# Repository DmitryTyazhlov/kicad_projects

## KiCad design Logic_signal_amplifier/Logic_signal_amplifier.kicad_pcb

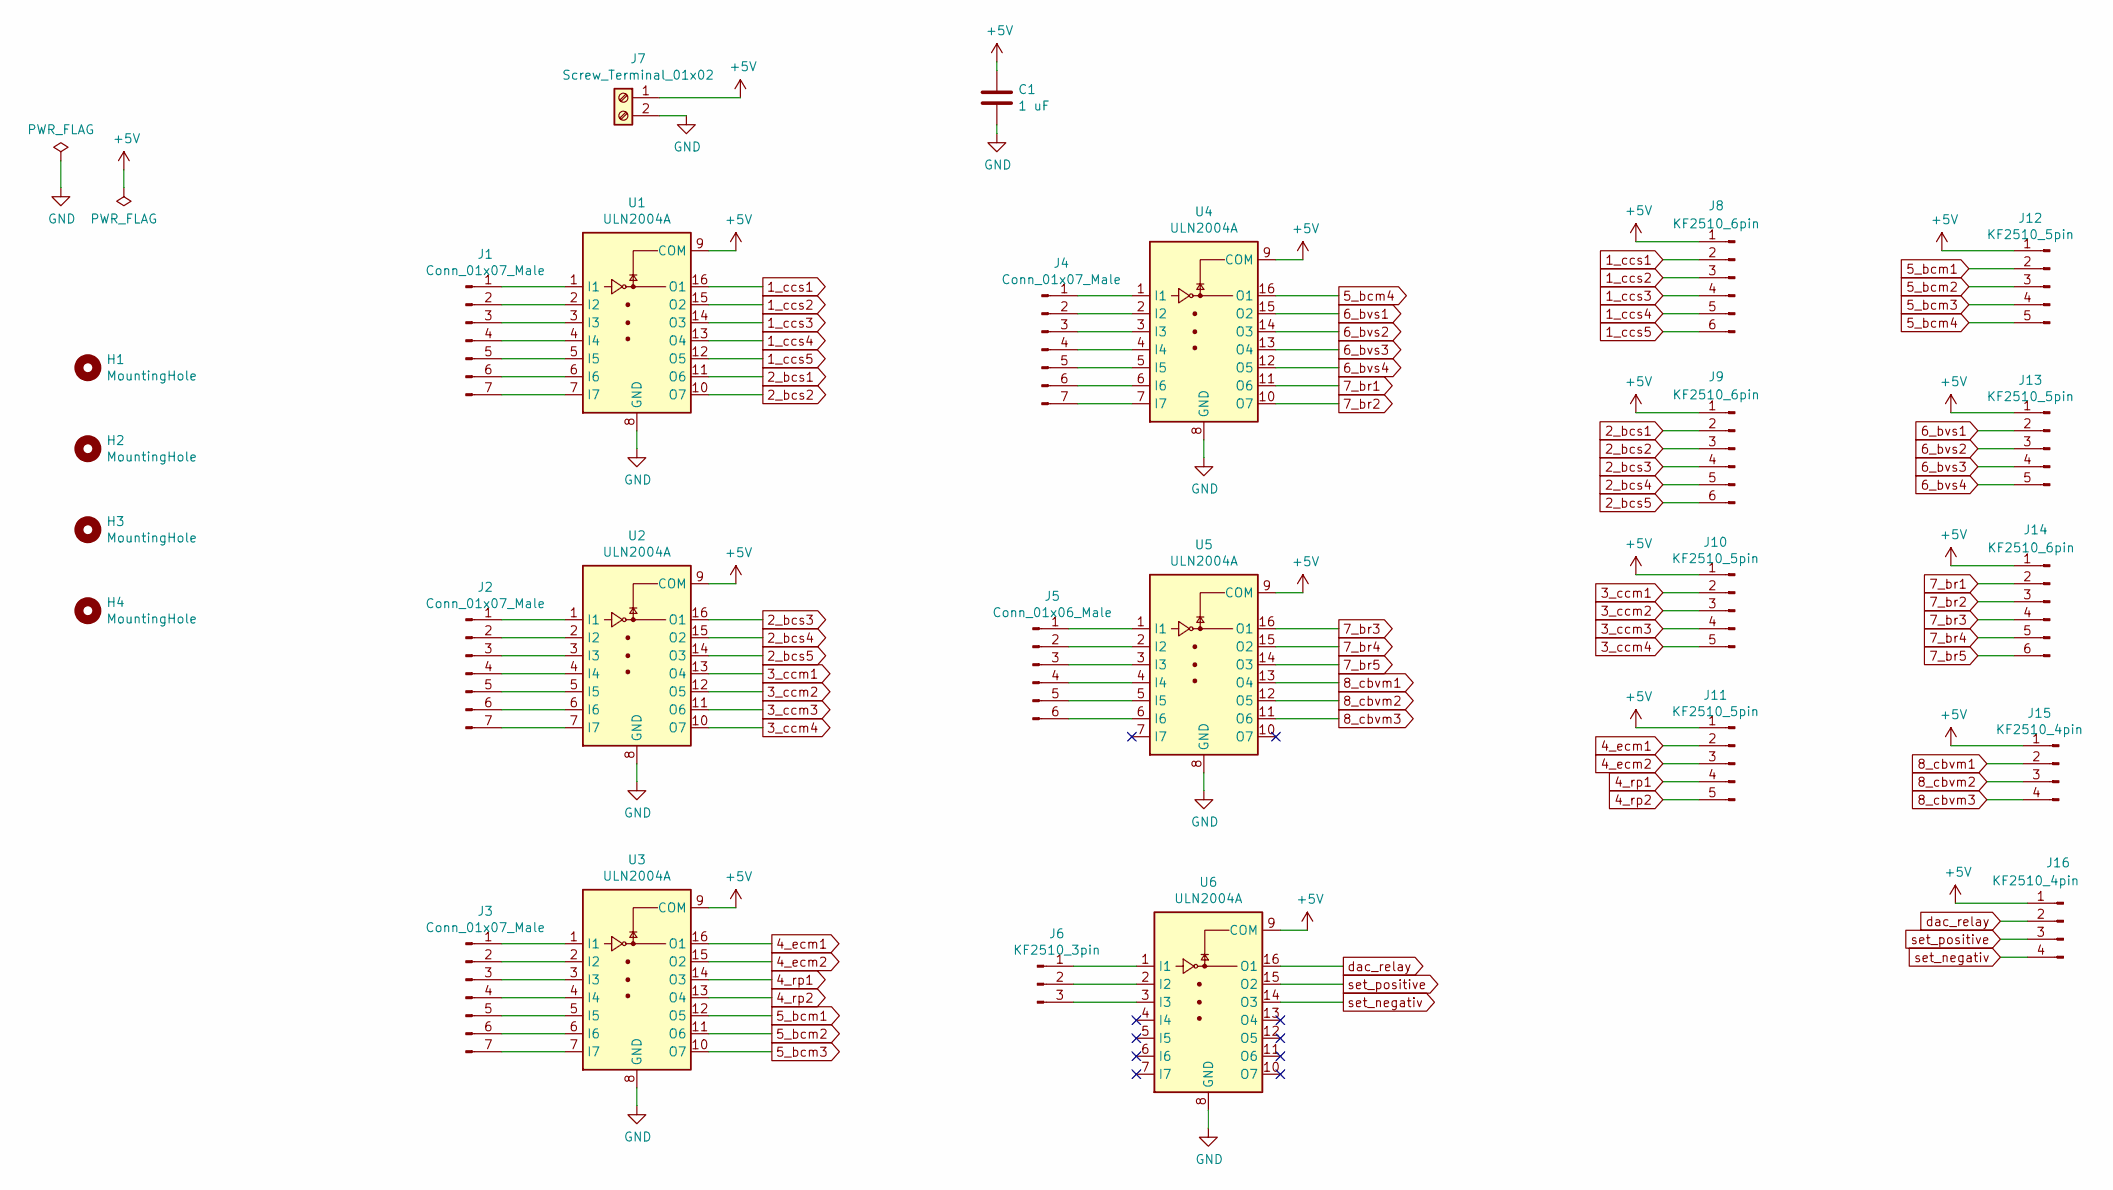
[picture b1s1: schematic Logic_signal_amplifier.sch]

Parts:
C1: 1 uF; C_0805_2012Metric
H1, H2, H3, H4: MountingHole; MountingHole_3.2mm_M3
J1, J2, J3, J4: Conn_01x07_Male; KF2510_7pin
J5: Conn_01x06_Male; KF2510_6pin
J6: KF2510_3pin
J7: Screw_Terminal_01x02; TerminalBlock_Phoenix_MKDS-1,5-2-5.08_1x02_P5.08mm_Horizont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
J8, J9, J14: KF2510_6pin
J10, J11, J12, J13: KF2510_5pin
J15, J16: KF2510_4pin
U1, U2, U3, U4, U5, U6: ULN2004A; SOIC-16_4.55x10.3mm_P1.27mm

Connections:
1_ccs1: J8.2, U1.16 (O1)
1_ccs2: J8.3, U1.15 (O2)
1_ccs3: J8.4, U1.14 (O3)
1_ccs4: J8.5, U1.13 (O4)
1_ccs5: J8.6, U1.12 (O5)
2_bcs1: J9.2, U1.11 (O6)
2_bcs2: J9.3, U1.10 (O7)
2_bcs3: J9.4, U2.16 (O1)
2_bcs4: J9.5, U2.15 (O2)
2_bcs5: J9.6, U2.14 (O3)
3_ccm1: J10.2, U2.13 (O4)
3_ccm2: J10.3, U2.12 (O5)
3_ccm3: J10.4, U2.11 (O6)
3_ccm4: J10.5, U2.10 (O7)
4_ecm1: J11.2, U3.16 (O1)
4_ecm2: J11.3, U3.15 (O2)
4_rp1: J11.4, U3.14 (O3)
4_rp2: J11.5, U3.13 (O4)
5_bcm1: J12.2, U3.12 (O5)
5_bcm2: J12.3, U3.11 (O6)
5_bcm3: J12.4, U3.10 (O7)
5_bcm4: J12.5, U4.16 (O1)
6_bvs1: J13.2, U4.15 (O2)
6_bvs2: J13.3, U4.14 (O3)
6_bvs3: J13.4, U4.13 (O4)
6_bvs4: J13.5, U4.12 (O5)
7_br1: J14.2, U4.11 (O6)
7_br2: J14.3, U4.10 (O7)
7_br3: J14.4, U5.16 (O1)
7_br4: J14.5, U5.15 (O2)
7_br5: J14.6, U5.14 (O3)
8_cbvm1: J15.2, U5.13 (O4)
8_cbvm2: J15.3, U5.12 (O5)
8_cbvm3: J15.4, U5.11 (O6)
+5V: C1.1, J7.1, J8.1, J9.1, J10.1, J11.1, J12.1, J13.1, J14.1, J15.1, J16.1, U1.9 (COM), U2.9 (COM), U3.9 (COM), U4.9 (COM), U5.9 (COM), U6.9 (COM)
GND: C1.2, J7.2, U1.8 (GND), U2.8 (GND), U3.8 (GND), U4.8 (GND), U5.8 (GND), U6.8 (GND)
unnamed: J1.1, U1.1 (I1)
unnamed: J1.2, U1.2 (I2)
unnamed: J1.3, U1.3 (I3)
unnamed: J1.4, U1.4 (I4)
unnamed: J1.5, U1.5 (I5)
unnamed: J1.6, U1.6 (I6)
unnamed: J1.7, U1.7 (I7)
unnamed: J2.1, U2.1 (I1)
unnamed: J2.2, U2.2 (I2)
unnamed: J2.3, U2.3 (I3)
unnamed: J2.4, U2.4 (I4)
unnamed: J2.5, U2.5 (I5)
unnamed: J2.6, U2.6 (I6)
unnamed: J2.7, U2.7 (I7)
unnamed: J3.1, U3.1 (I1)
unnamed: J3.2, U3.2 (I2)
unnamed: J3.3, U3.3 (I3)
unnamed: J3.4, U3.4 (I4)
unnamed: J3.5, U3.5 (I5)
unnamed: J3.6, U3.6 (I6)
unnamed: J3.7, U3.7 (I7)
unnamed: J4.1, U4.1 (I1)
unnamed: J4.2, U4.2 (I2)
unnamed: J4.3, U4.3 (I3)
unnamed: J4.4, U4.4 (I4)
unnamed: J4.5, U4.5 (I5)
unnamed: J4.6, U4.6 (I6)
unnamed: J4.7, U4.7 (I7)
unnamed: J5.1, U5.1 (I1)
unnamed: J5.2, U5.2 (I2)
unnamed: J5.3, U5.3 (I3)
unnamed: J5.4, U5.4 (I4)
unnamed: J5.5, U5.5 (I5)
unnamed: J5.6, U5.6 (I6)
unnamed: J6.1, U6.1 (I1)
unnamed: J6.2, U6.2 (I2)
unnamed: J6.3, U6.3 (I3)
dac_relay: J16.2, U6.16 (O1)
set_negativ: J16.4, U6.14 (O3)
set_positive: J16.3, U6.15 (O2)

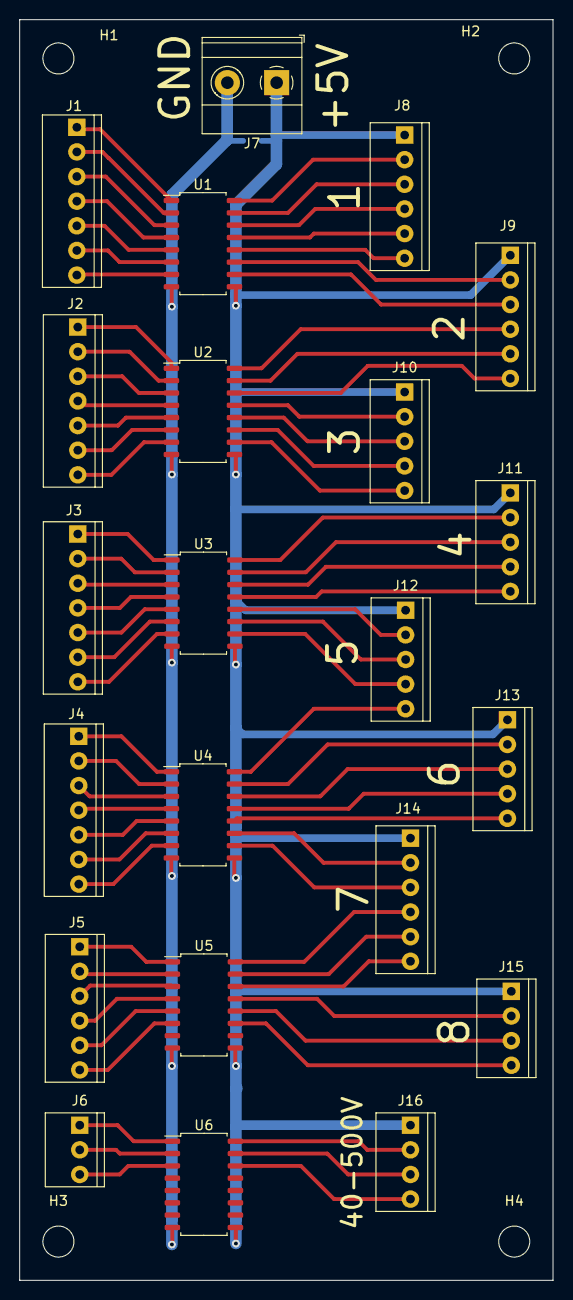
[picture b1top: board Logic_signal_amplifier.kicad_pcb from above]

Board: 2 copper layers, 55.0 x 130.0 mm, 27 parts (1 on the bottom side), 76 nets.

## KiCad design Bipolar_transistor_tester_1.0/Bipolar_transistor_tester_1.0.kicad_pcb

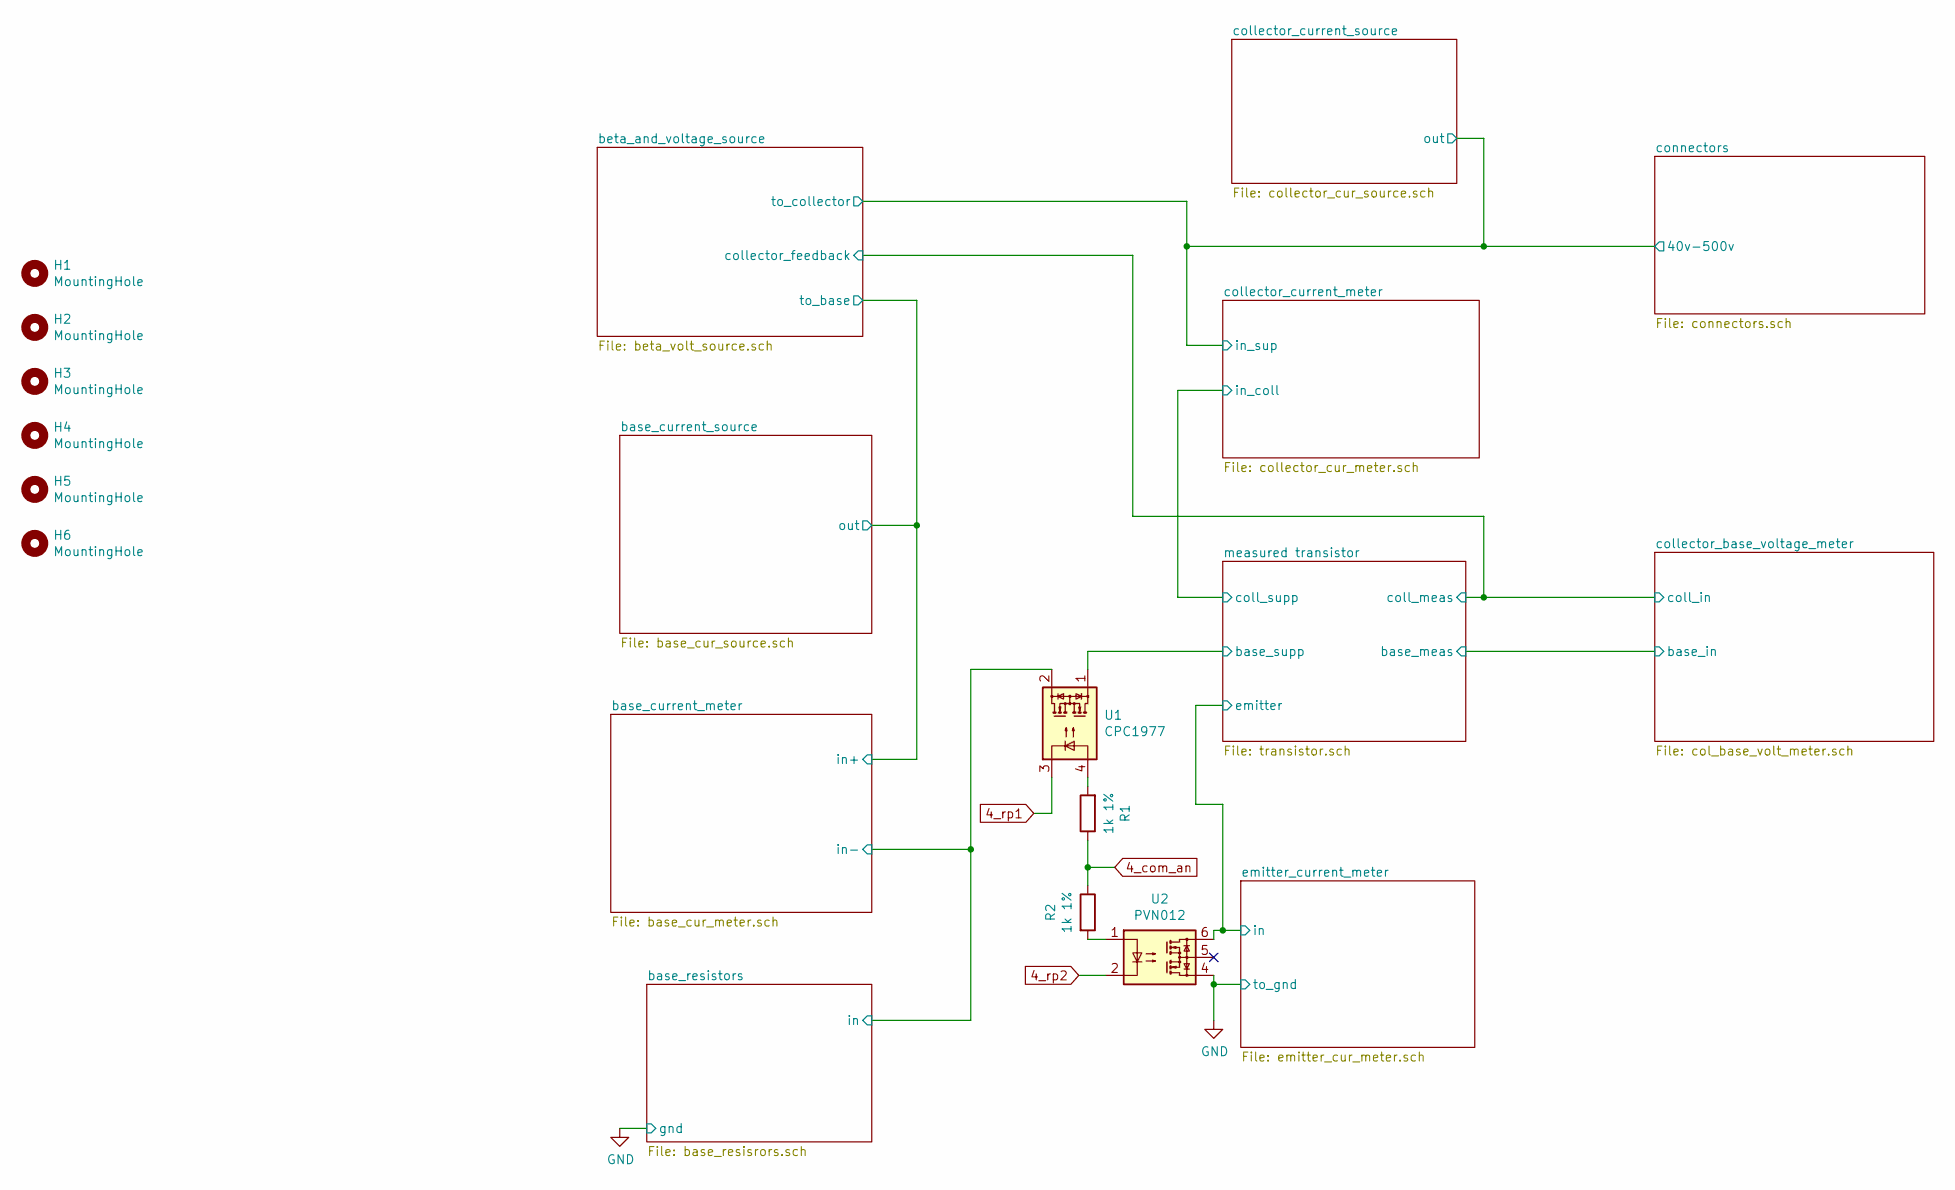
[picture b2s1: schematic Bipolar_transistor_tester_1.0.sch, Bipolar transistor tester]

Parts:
H1, H2, H3, H4, H5, H6: MountingHole; MountingHole_3.2mm_M3
R1, R2: 1k 1%; R_0805_2012Metric
U1: CPC1977; i4-PAC
U2: PVN012; DIP-6_W7.62mm

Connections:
4_com_an: R1.1, R2.1; also elsewhere on the board
4_rp1: U1.3; also elsewhere on the board
4_rp2: U2.2; also elsewhere on the board
/base_resistors/in: U1.2; also elsewhere on the board
/measured transistor/base_supp: U1.1; also elsewhere on the board
/measured transistor/emitter: U2.6; also elsewhere on the board
GND: U2.4; also elsewhere on the board
unnamed: R1.2, U1.4
unnamed: R2.2, U2.1

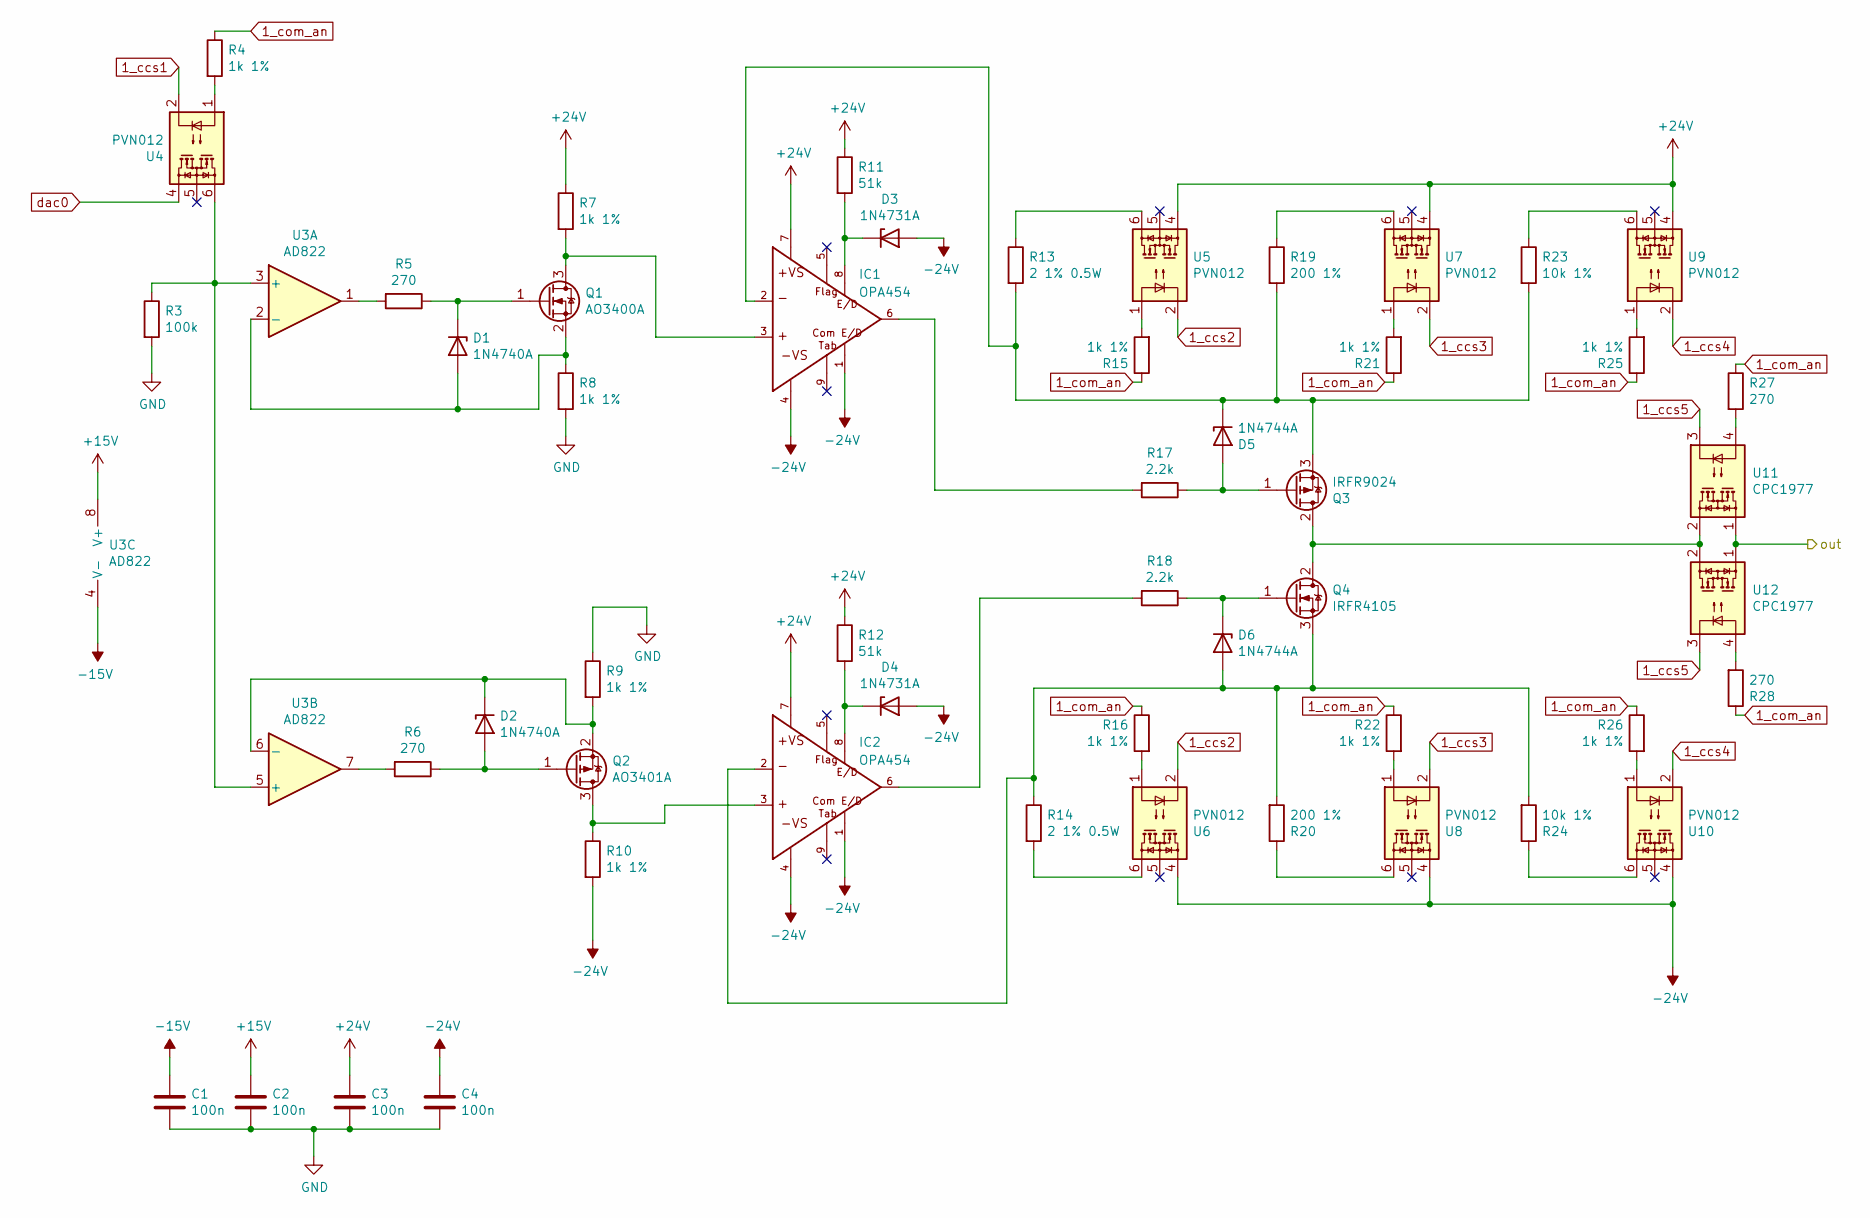
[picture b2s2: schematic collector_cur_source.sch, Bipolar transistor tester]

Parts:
C1, C2, C3, C4: 100n; C_0805_2012Metric
D1, D2: 1N4740A; D_DO-41_SOD81_P10.16mm_Horizontal
D3, D4: 1N4731A; D_DO-41_SOD81_P10.16mm_Horizontal
D5, D6: 1N4744A; D_DO-41_SOD81_P10.16mm_Horizontal
IC1, IC2: OPA454; SOIC-8-1EP_3.9x4.9mm_P1.27mm_EP2.29x3mm; PARTNUM 296-22997-5-ND
Q1: AO3400A; SOT-23
Q2: AO3401A; SOT-23
Q3: IRFR9024; TO-252-2
Q4: IRFR4105; TO-252-2
R3: 100k; R_0805_2012Metric
R4, R7, R8, R9, R10, R15, R16, R21, R22, R25, R26: 1k 1%; R_0805_2012Metric
R5, R6, R27, R28: 270; R_0805_2012Metric
R11, R12: 51k; R_0805_2012Metric
R13, R14: 2 1% 0.5W; R_Axial_DIN0309_L9.0mm_D3.2mm_P12.70mm_Horizontal
R17, R18: 2.2k; R_0805_2012Metric
R19, R20: 200 1%; R_0805_2012Metric
R23, R24: 10k 1%; R_0805_2012Metric
U3: AD822; DIP-8_W7.62mm
U4, U5, U6, U7, U8, U9, U10: PVN012; DIP-6_W7.62mm
U11, U12: CPC1977; i4-PAC

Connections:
1_ccs1: U4.2; also elsewhere on the board
1_ccs2: U5.2, U6.2; also elsewhere on the board
1_ccs3: U7.2, U8.2; also elsewhere on the board
1_ccs4: U9.2, U10.2; also elsewhere on the board
1_ccs5: U11.3, U12.3; also elsewhere on the board
1_com_an: R4.1, R15.1, R16.1, R21.1, R22.1, R25.1, R26.1, R27.1, R28.1; also elsewhere on the board
+15V: C2.1, U3.8 (V+); also elsewhere on the board
+24V: C3.1, IC1.7, IC2.7, R7.1, R11.1, R12.1, U5.4, U7.4, U9.4; also elsewhere on the board
-15V: C1.1, U3.4 (V-); also elsewhere on the board
-24V: C4.1, D3.2 (A), D4.2 (A), IC1.1, IC1.4, IC2.1, IC2.4, R10.2, U6.4, U8.4, U10.4; also elsewhere on the board
/connectors/40v-500v: U11.1, U12.1; also elsewhere on the board
GND: C1.2, C2.2, C3.2, C4.2, R3.2, R8.2, R9.1; also elsewhere on the board
unnamed: D1.1 (K), Q1.1 (G), R5.1
unnamed: D1.2 (A), Q1.2 (S), R8.1, U3.2 (-)
unnamed: D2.1 (K), Q2.2 (S), R9.2, U3.6 (-)
unnamed: D2.2 (A), Q2.1 (G), R6.1
unnamed: D3.1 (K), IC1.8, R11.2
unnamed: D4.1 (K), IC2.8, R12.2
unnamed: D5.1 (K), IC1.2, Q3.3 (S), R13.2, R19.2, R23.2
unnamed: D5.2 (A), Q3.1 (G), R17.1
unnamed: D6.1 (K), Q4.1 (G), R18.1
unnamed: D6.2 (A), IC2.2, Q4.3 (S), R14.1, R20.2, R24.2
unnamed: IC1.3, Q1.3 (D), R7.2
unnamed: IC1.6, R17.2
unnamed: IC2.3, Q2.3 (D), R10.1
unnamed: IC2.6, R18.2
unnamed: Q3.2 (D), Q4.2 (D), U11.2, U12.2
unnamed: R3.1, U3.3 (+), U3.5 (+), U4.6
unnamed: R4.2, U4.1
unnamed: R5.2, U3.1
unnamed: R6.2, U3.7
unnamed: R13.1, U5.6
unnamed: R14.2, U6.6
unnamed: R15.2, U5.1
unnamed: R16.2, U6.1
unnamed: R19.1, U7.6
unnamed: R20.1, U8.6
unnamed: R21.2, U7.1
unnamed: R22.2, U8.1
unnamed: R23.1, U9.6
unnamed: R24.1, U10.6
unnamed: R25.2, U9.1
unnamed: R26.2, U10.1
unnamed: R27.2, U11.4
unnamed: R28.2, U12.4
dac0: U4.4; also elsewhere on the board

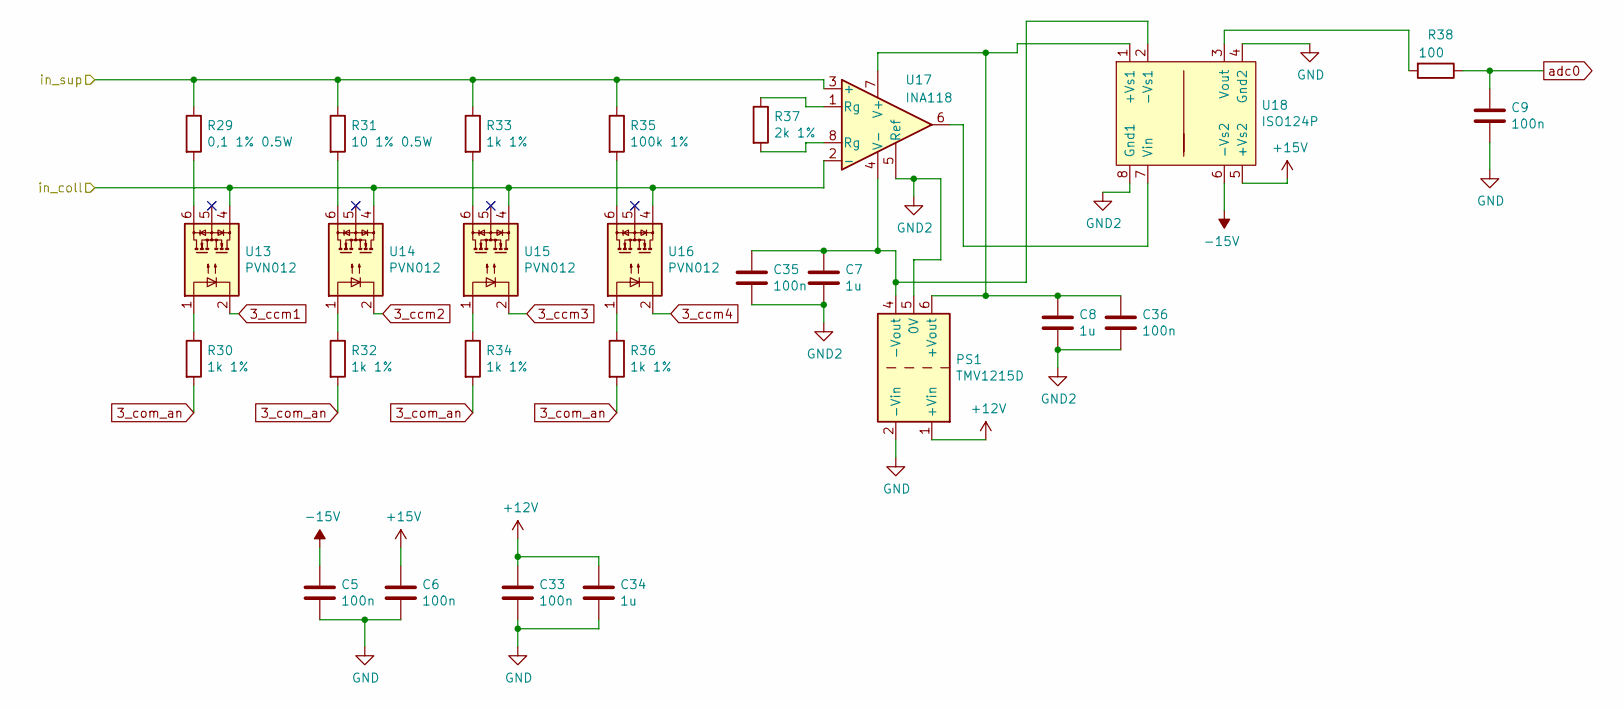
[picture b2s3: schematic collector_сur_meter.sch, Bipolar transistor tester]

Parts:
C5, C6, C9, C33, C35, C36: 100n; C_0805_2012Metric
C7, C8, C34: 1u; C_0805_2012Metric
PS1: TMV1215D; Converter_DCDC_XP_POWER-IHxxxxSH_THT
R29: 0,1 1% 0.5W; R_Axial_DIN0309_L9.0mm_D3.2mm_P12.70mm_Horizontal
R30, R32, R33, R34, R36: 1k 1%; R_0805_2012Metric
R31: 10 1% 0.5W; R_Axial_DIN0309_L9.0mm_D3.2mm_P12.70mm_Horizontal
R35: 100k 1%; R_0805_2012Metric
R37: 2k 1%; R_0805_2012Metric
R38: 100; R_0805_2012Metric
U13, U14, U15, U16: PVN012; DIP-6_W7.62mm
U17: INA118; DIP-8_W7.62mm
U18: ISO124P; DIP-8-16_W7.62mm

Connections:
3_ccm1: U13.2; also elsewhere on the board
3_ccm2: U14.2; also elsewhere on the board
3_ccm3: U15.2; also elsewhere on the board
3_ccm4: U16.2; also elsewhere on the board
3_com_an: R30.2, R32.2, R34.2, R36.2; also elsewhere on the board
+12V: C33.1, C34.1, PS1.1 (+Vin); also elsewhere on the board
+15V: C6.1, U18.5 (+Vs2); also elsewhere on the board
-15V: C5.1, U18.6 (-Vs2); also elsewhere on the board
/connectors/40v-500v: R29.1, R31.1, R33.1, R35.1, U17.3 (+); also elsewhere on the board
/measured transistor/coll_supp: U13.4, U14.4, U15.4, U16.4, U17.2 (-); also elsewhere on the board
GND: C5.2, C6.2, C9.2, C33.2, C34.2, PS1.2 (-Vin), U18.4 (Gnd2); also elsewhere on the board
GND2: C7.2, C8.2, C35.2, C36.2, PS1.5 (0V), U17.5 (Ref), U18.8 (Gnd1)
unnamed: C7.1, C35.1, PS1.4 (-Vout), U17.4 (V-), U18.2 (-Vs1)
unnamed: C8.1, C36.1, PS1.6 (+Vout), U17.7 (V+), U18.1 (+Vs1)
unnamed: R29.2, U13.6
unnamed: R30.1, U13.1
unnamed: R31.2, U14.6
unnamed: R32.1, U14.1
unnamed: R33.2, U15.6
unnamed: R34.1, U15.1
unnamed: R35.2, U16.6
unnamed: R36.1, U16.1
unnamed: R37.1, U17.1 (Rg)
unnamed: R37.2, U17.8 (Rg)
unnamed: R38.2, U18.3 (Vout)
unnamed: U17.6, U18.7 (Vin)
adc0: C9.1, R38.1; also elsewhere on the board

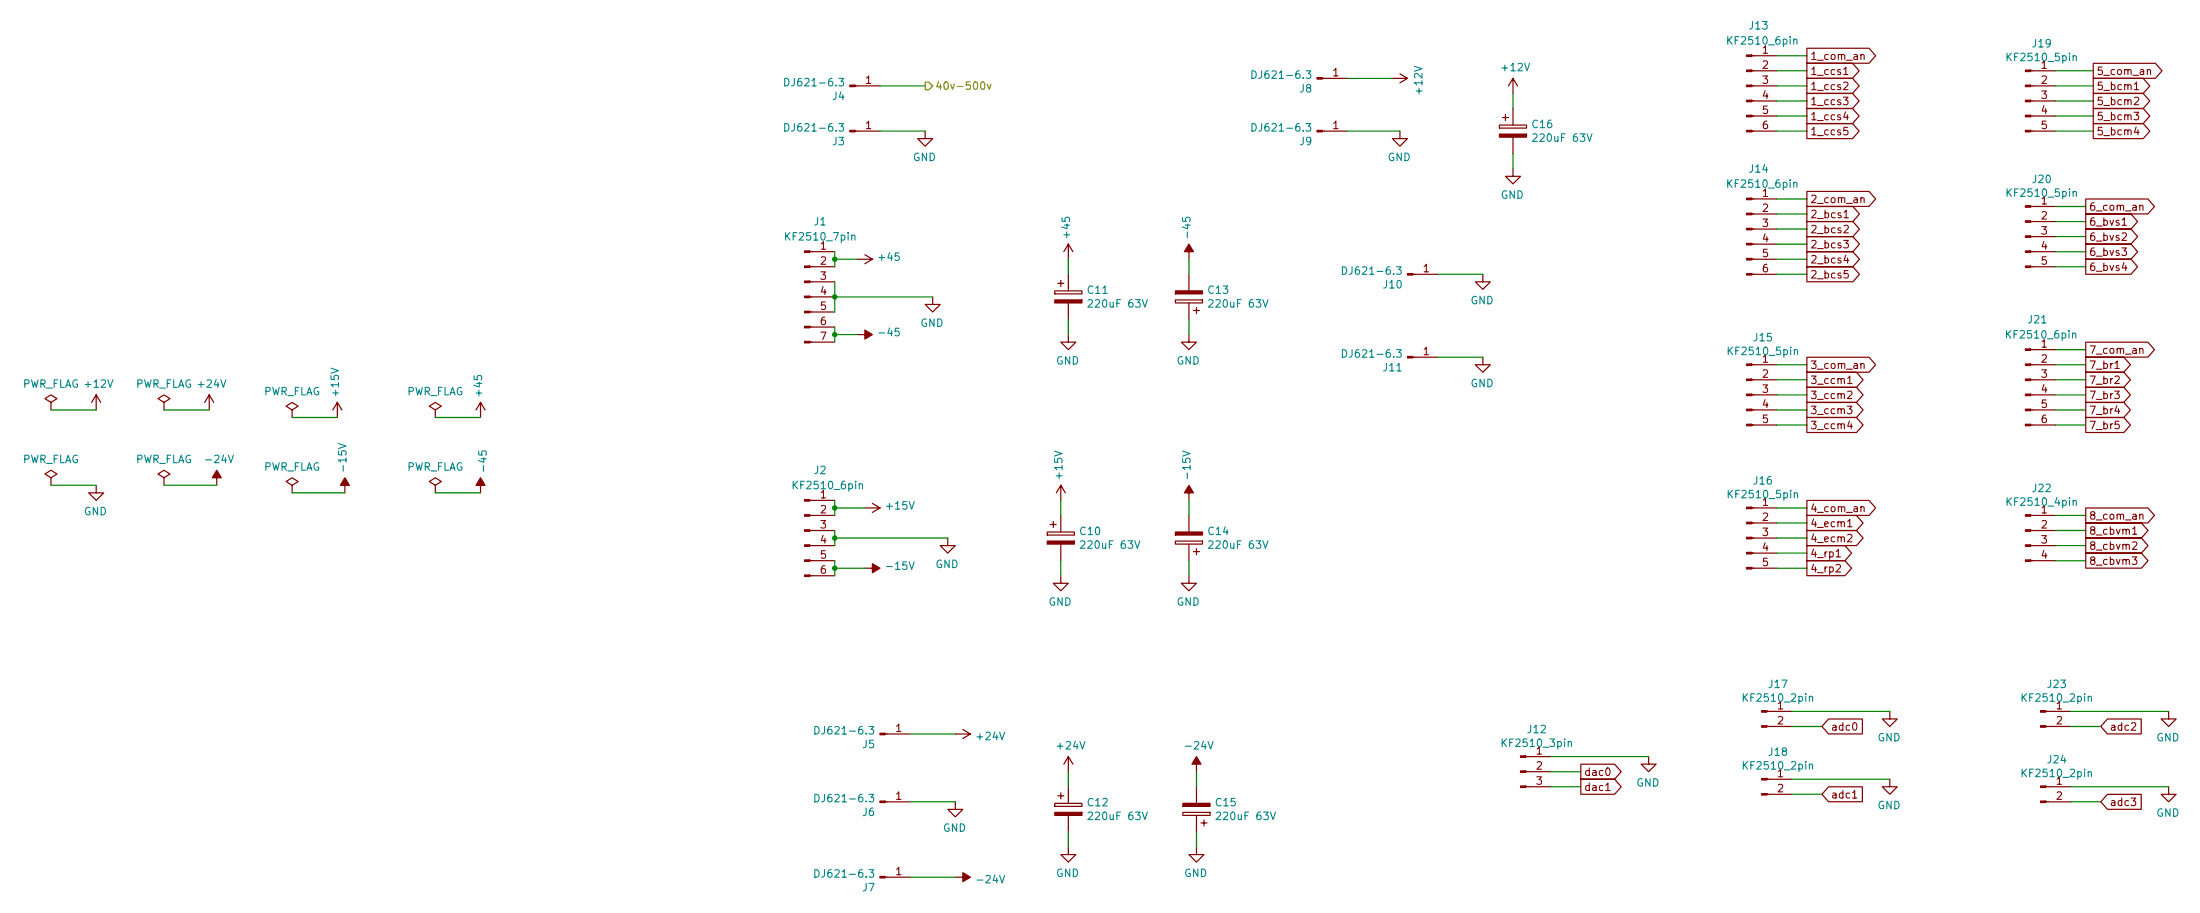
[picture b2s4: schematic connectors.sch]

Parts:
C10, C11, C12, C13, C14, C15, C16: 220uF 63V; CP_Radial_D10.0mm_P5.00mm
J1: KF2510_7pin
J2, J13, J14, J21: KF2510_6pin
J3, J4, J5, J6, J7, J8, J9, J10, J11: DJ621-6.3; Knife_Terminal_6.3mm_P5.00mm_Vertical
J12: KF2510_3pin
J15, J16, J19, J20: KF2510_5pin
J17, J18, J23, J24: KF2510_2pin
J22: KF2510_4pin

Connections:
1_ccs1: J13.2; also elsewhere on the board
1_ccs2: J13.3; also elsewhere on the board
1_ccs3: J13.4; also elsewhere on the board
1_ccs4: J13.5; also elsewhere on the board
1_ccs5: J13.6; also elsewhere on the board
1_com_an: J13.1; also elsewhere on the board
2_bcs1: J14.2; also elsewhere on the board
2_bcs2: J14.3; also elsewhere on the board
2_bcs3: J14.4; also elsewhere on the board
2_bcs4: J14.5; also elsewhere on the board
2_bcs5: J14.6; also elsewhere on the board
2_com_an: J14.1; also elsewhere on the board
3_ccm1: J15.2; also elsewhere on the board
3_ccm2: J15.3; also elsewhere on the board
3_ccm3: J15.4; also elsewhere on the board
3_ccm4: J15.5; also elsewhere on the board
3_com_an: J15.1; also elsewhere on the board
4_com_an: J16.1; also elsewhere on the board
4_ecm1: J16.2; also elsewhere on the board
4_ecm2: J16.3; also elsewhere on the board
4_rp1: J16.4; also elsewhere on the board
4_rp2: J16.5; also elsewhere on the board
5_bcm1: J19.2; also elsewhere on the board
5_bcm2: J19.3; also elsewhere on the board
5_bcm3: J19.4; also elsewhere on the board
5_bcm4: J19.5; also elsewhere on the board
5_com_an: J19.1; also elsewhere on the board
6_bvs1: J20.2; also elsewhere on the board
6_bvs2: J20.3; also elsewhere on the board
6_bvs3: J20.4; also elsewhere on the board
6_bvs4: J20.5; also elsewhere on the board
6_com_an: J20.1; also elsewhere on the board
7_br1: J21.2; also elsewhere on the board
7_br2: J21.3; also elsewhere on the board
7_br3: J21.4; also elsewhere on the board
7_br4: J21.5; also elsewhere on the board
7_br5: J21.6; also elsewhere on the board
7_com_an: J21.1; also elsewhere on the board
8_cbvm1: J22.2; also elsewhere on the board
8_cbvm2: J22.3; also elsewhere on the board
8_cbvm3: J22.4; also elsewhere on the board
8_com_an: J22.1; also elsewhere on the board
+12V: C16.1, J8.1; also elsewhere on the board
+15V: C10.1, J2.1, J2.2; also elsewhere on the board
+24V: C12.1, J5.1; also elsewhere on the board
+45V: C11.1, J1.1, J1.2; also elsewhere on the board
-15V: C14.2, J2.5, J2.6; also elsewhere on the board
-24V: C15.2, J7.1; also elsewhere on the board
-45V: C13.2, J1.6, J1.7; also elsewhere on the board
/connectors/40v-500v: J4.1; also elsewhere on the board
GND: C10.2, C11.2, C12.2, C13.1, C14.1, C15.1, C16.2, J1.3, J1.4, J1.5, J2.3, J2.4, J3.1, J6.1, J9.1, J10.1, J11.1, J12.1, J17.1, J18.1, J23.1, J24.1; also elsewhere on the board
adc0: J17.2; also elsewhere on the board
adc1: J18.2; also elsewhere on the board
adc2: J23.2; also elsewhere on the board
adc3: J24.2; also elsewhere on the board
dac0: J12.2; also elsewhere on the board
dac1: J12.3; also elsewhere on the board

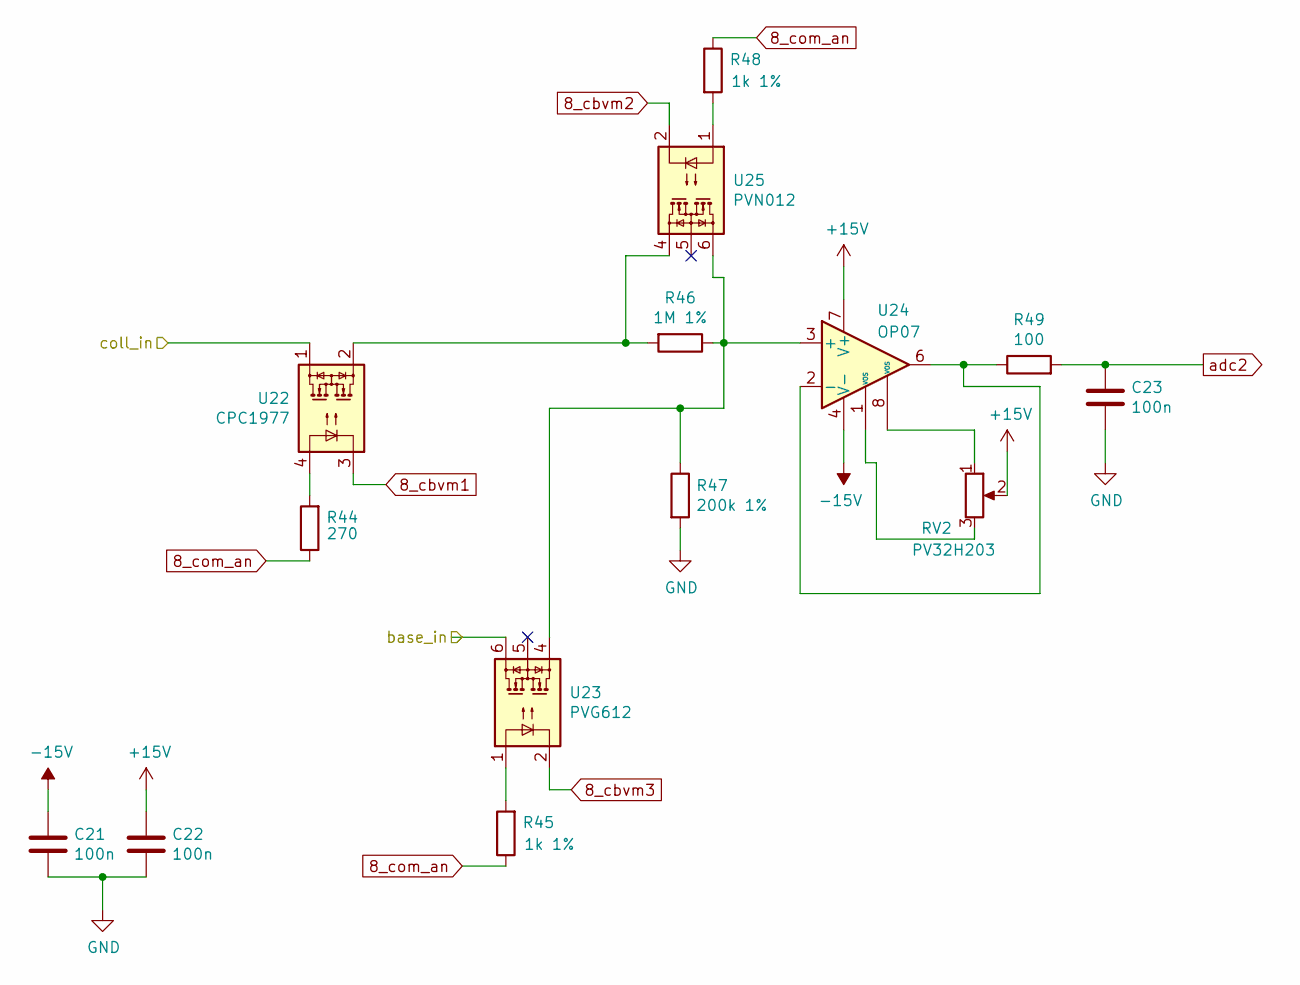
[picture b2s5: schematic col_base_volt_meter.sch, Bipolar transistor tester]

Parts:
C21, C22, C23: 100n; C_0805_2012Metric
R44: 270; R_0805_2012Metric
R45, R48: 1k 1%; R_0805_2012Metric
R46: 1M 1%; R_0805_2012Metric
R47: 200k 1%; R_0805_2012Metric
R49: 100; R_0805_2012Metric
RV2: PV32H203; Potentiometer_Bourns_3339H_Vertical
U22: CPC1977; i4-PAC
U23: PVG612; DIP-6_W7.62mm
U24: OP07; DIP-8_W7.62mm
U25: PVN012; DIP-6_W7.62mm

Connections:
8_cbvm1: U22.3; also elsewhere on the board
8_cbvm2: U25.2; also elsewhere on the board
8_cbvm3: U23.2; also elsewhere on the board
8_com_an: R44.1, R45.1, R48.1; also elsewhere on the board
+15V: C22.1, RV2.2, U24.7 (V+); also elsewhere on the board
-15V: C21.1, U24.4 (V-); also elsewhere on the board
/collector_base_voltage_meter/base_in: U23.6; also elsewhere on the board
/collector_base_voltage_meter/coll_in: U22.1; also elsewhere on the board
GND: C21.2, C22.2, C23.2, R47.2; also elsewhere on the board
unnamed: R44.2, U22.4
unnamed: R45.2, U23.1
unnamed: R46.1, R47.1, U23.4, U24.3 (+), U25.6
unnamed: R46.2, U22.2, U25.4
unnamed: R48.2, U25.1
unnamed: R49.1, U24.2 (-), U24.6
unnamed: RV2.1, U24.8 (VOS)
unnamed: RV2.3, U24.1 (VOS)
adc2: C23.1, R49.2; also elsewhere on the board

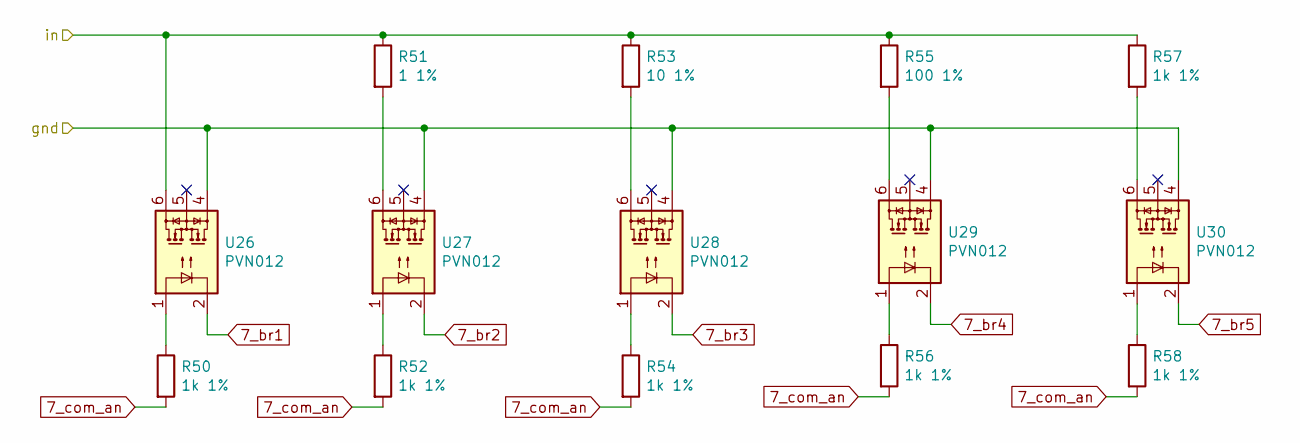
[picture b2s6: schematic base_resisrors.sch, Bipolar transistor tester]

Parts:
R50, R52, R54, R56, R57, R58: 1k 1%; R_0805_2012Metric
R51: 1 1%; R_0805_2012Metric
R53: 10 1%; R_0805_2012Metric
R55: 100 1%; R_0805_2012Metric
U26, U27, U28, U29, U30: PVN012; DIP-6_W7.62mm

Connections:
7_br1: U26.2; also elsewhere on the board
7_br2: U27.2; also elsewhere on the board
7_br3: U28.2; also elsewhere on the board
7_br4: U29.2; also elsewhere on the board
7_br5: U30.2; also elsewhere on the board
7_com_an: R50.2, R52.2, R54.2, R56.2, R58.2; also elsewhere on the board
/base_resistors/in: R51.1, R53.1, R55.1, R57.1, U26.6; also elsewhere on the board
GND: U26.4, U27.4, U28.4, U29.4, U30.4; also elsewhere on the board
unnamed: R50.1, U26.1
unnamed: R51.2, U27.6
unnamed: R52.1, U27.1
unnamed: R53.2, U28.6
unnamed: R54.1, U28.1
unnamed: R55.2, U29.6
unnamed: R56.1, U29.1
unnamed: R57.2, U30.6
unnamed: R58.1, U30.1

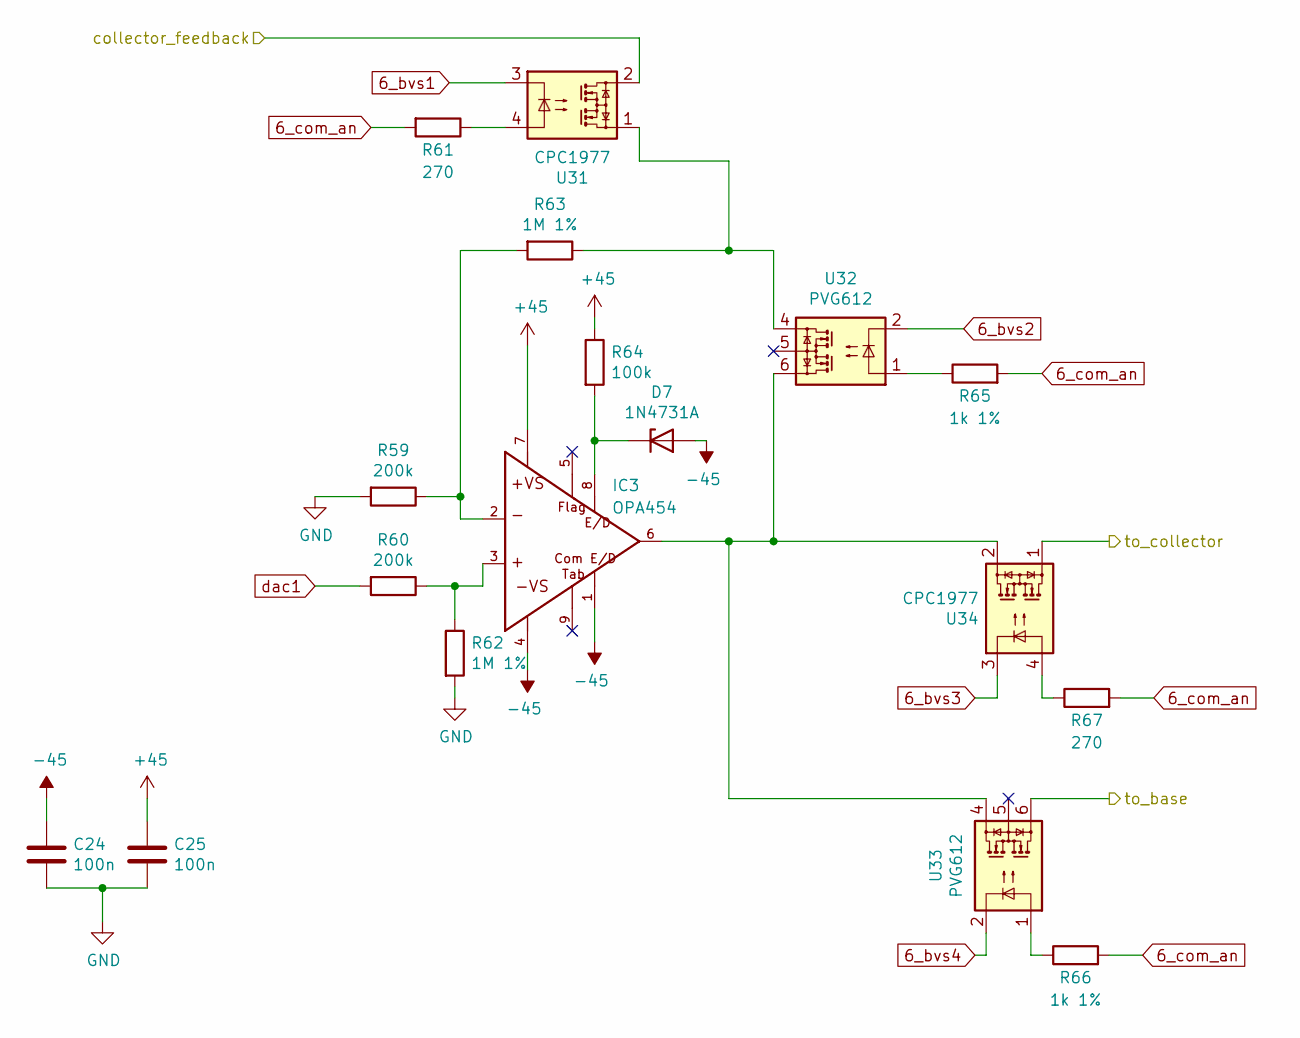
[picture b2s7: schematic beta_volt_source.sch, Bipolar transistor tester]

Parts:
C24, C25: 100n; C_0805_2012Metric
D7: 1N4731A; D_DO-41_SOD81_P10.16mm_Horizontal
IC3: OPA454; SOIC-8-1EP_3.9x4.9mm_P1.27mm_EP2.29x3mm; PARTNUM 296-22997-5-ND
R59, R60: 200k; R_0805_2012Metric
R61, R67: 270; R_0805_2012Metric
R62, R63: 1M 1%; R_0805_2012Metric
R64: 100k; R_0805_2012Metric
R65, R66: 1k 1%; R_0805_2012Metric
U31, U34: CPC1977; i4-PAC
U32, U33: PVG612; DIP-6_W7.62mm

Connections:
6_bvs1: U31.3; also elsewhere on the board
6_bvs2: U32.2; also elsewhere on the board
6_bvs3: U34.3; also elsewhere on the board
6_bvs4: U33.2; also elsewhere on the board
6_com_an: R61.2, R65.2, R66.2, R67.2; also elsewhere on the board
+45V: C25.1, IC3.7, R64.1; also elsewhere on the board
-45V: C24.1, D7.2 (A), IC3.1, IC3.4; also elsewhere on the board
/base_current_meter/in+: U33.6; also elsewhere on the board
/collector_base_voltage_meter/coll_in: U31.2; also elsewhere on the board
/connectors/40v-500v: U34.1; also elsewhere on the board
GND: C24.2, C25.2, R59.2, R62.2; also elsewhere on the board
unnamed: D7.1 (K), IC3.8, R64.2
unnamed: IC3.2, R59.1, R63.2
unnamed: IC3.3, R60.1, R62.1
unnamed: IC3.6, U32.6, U33.4, U34.2
unnamed: R61.1, U31.4
unnamed: R63.1, U31.1, U32.4
unnamed: R65.1, U32.1
unnamed: R66.1, U33.1
unnamed: R67.1, U34.4
dac1: R60.2; also elsewhere on the board
